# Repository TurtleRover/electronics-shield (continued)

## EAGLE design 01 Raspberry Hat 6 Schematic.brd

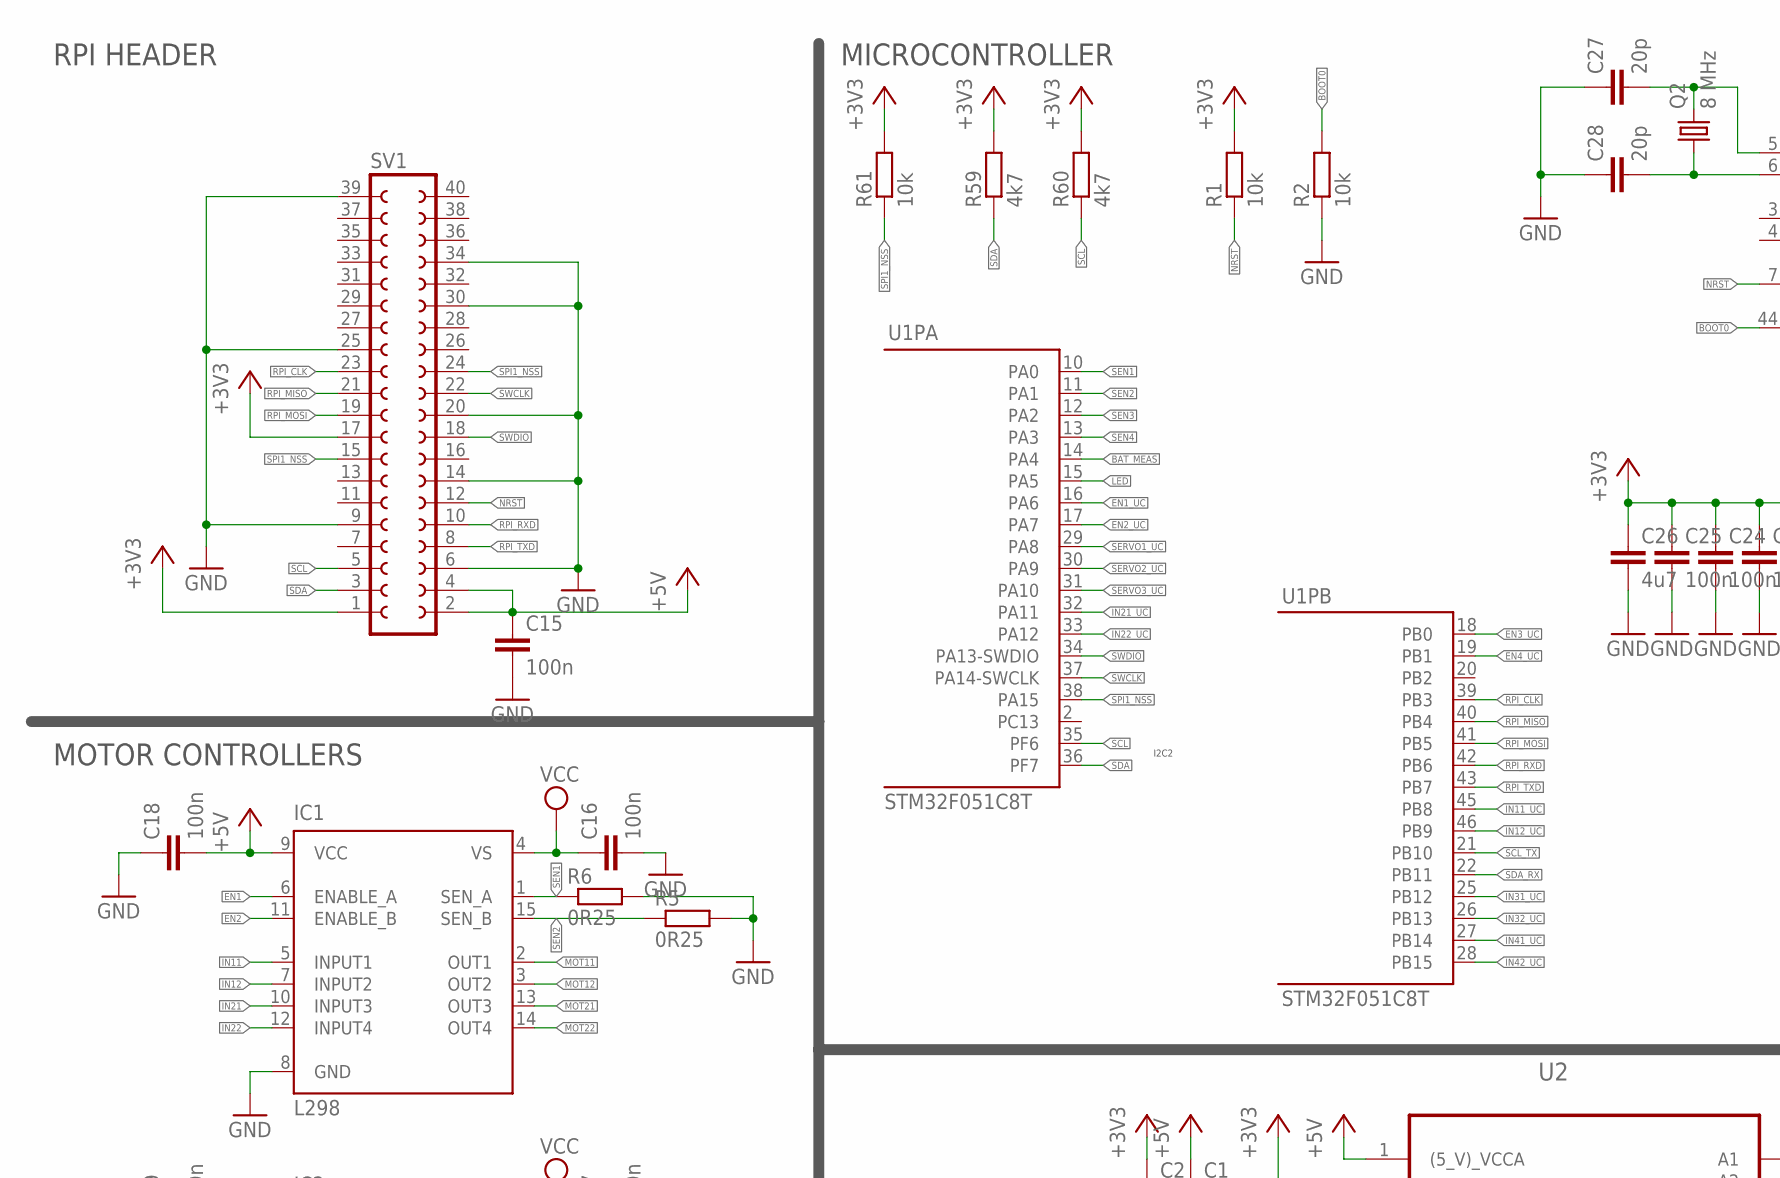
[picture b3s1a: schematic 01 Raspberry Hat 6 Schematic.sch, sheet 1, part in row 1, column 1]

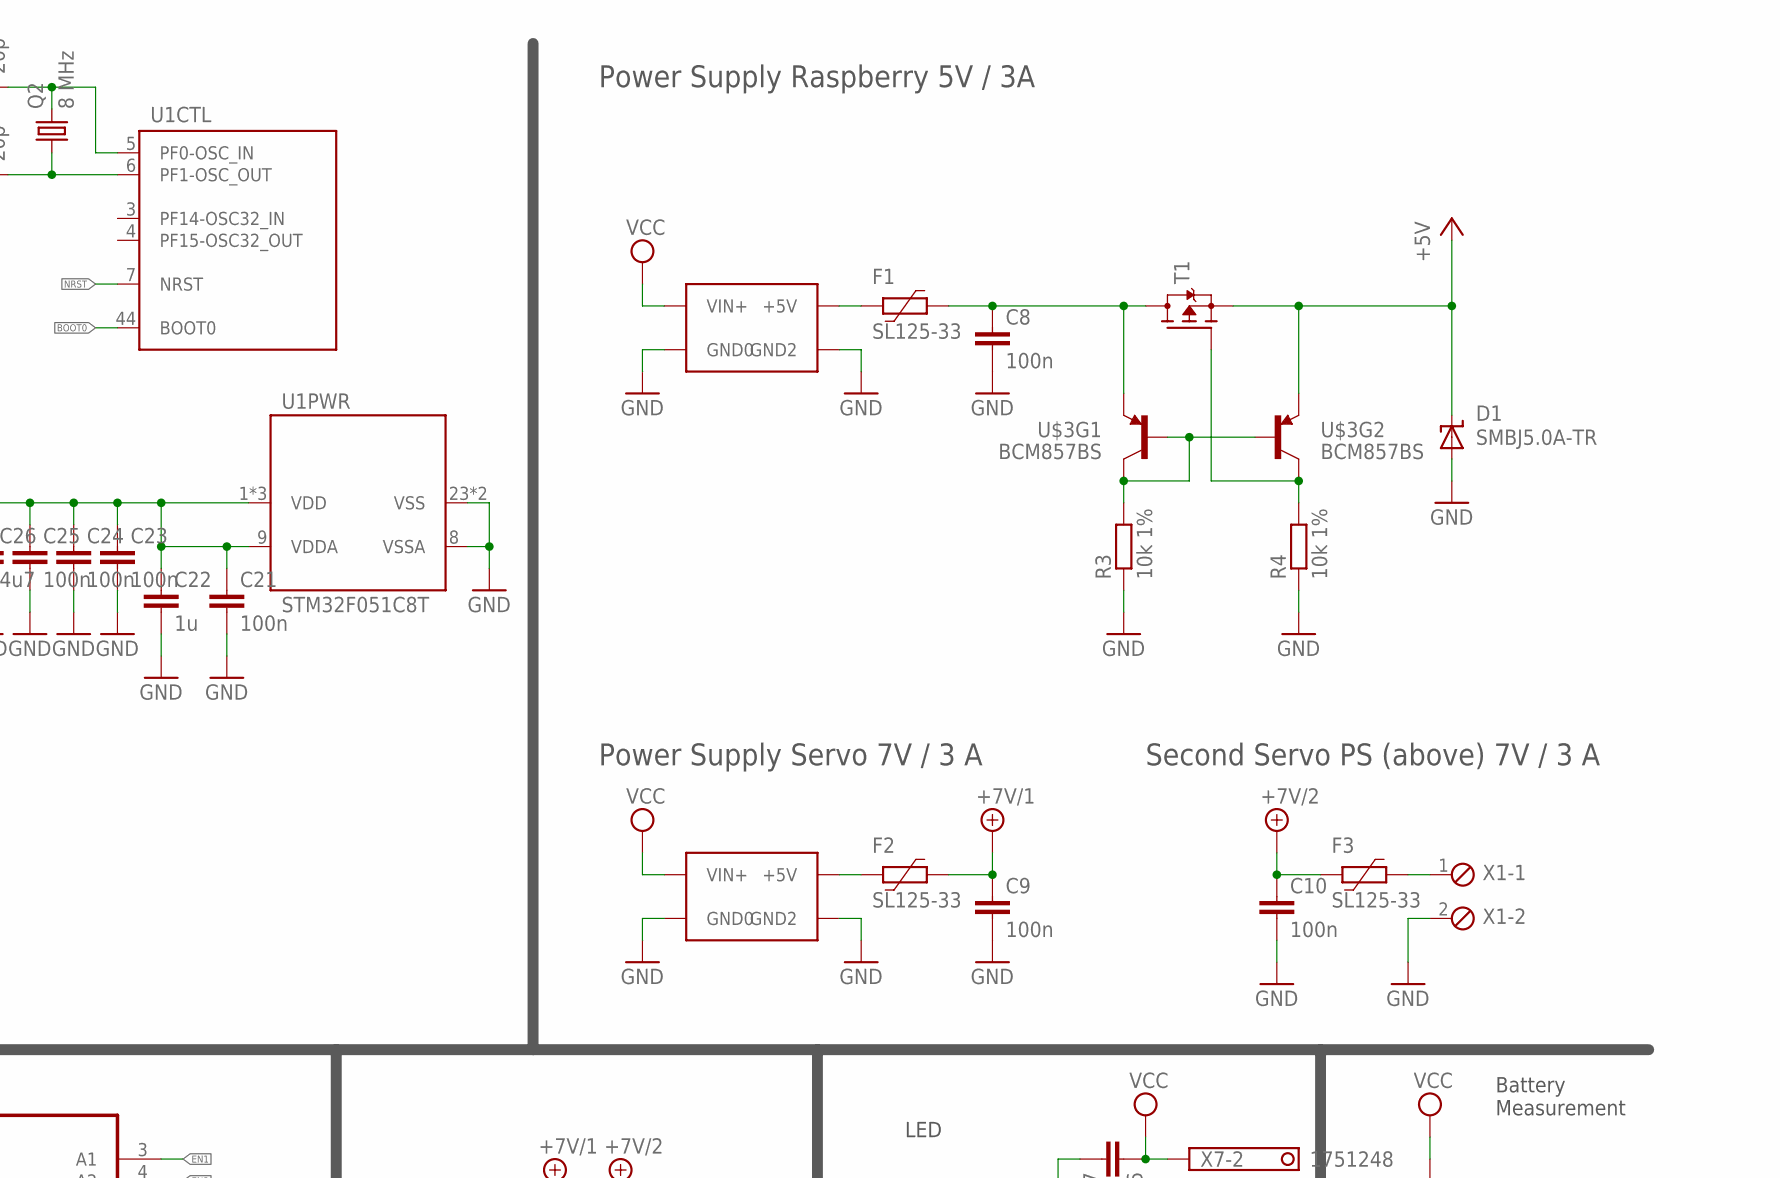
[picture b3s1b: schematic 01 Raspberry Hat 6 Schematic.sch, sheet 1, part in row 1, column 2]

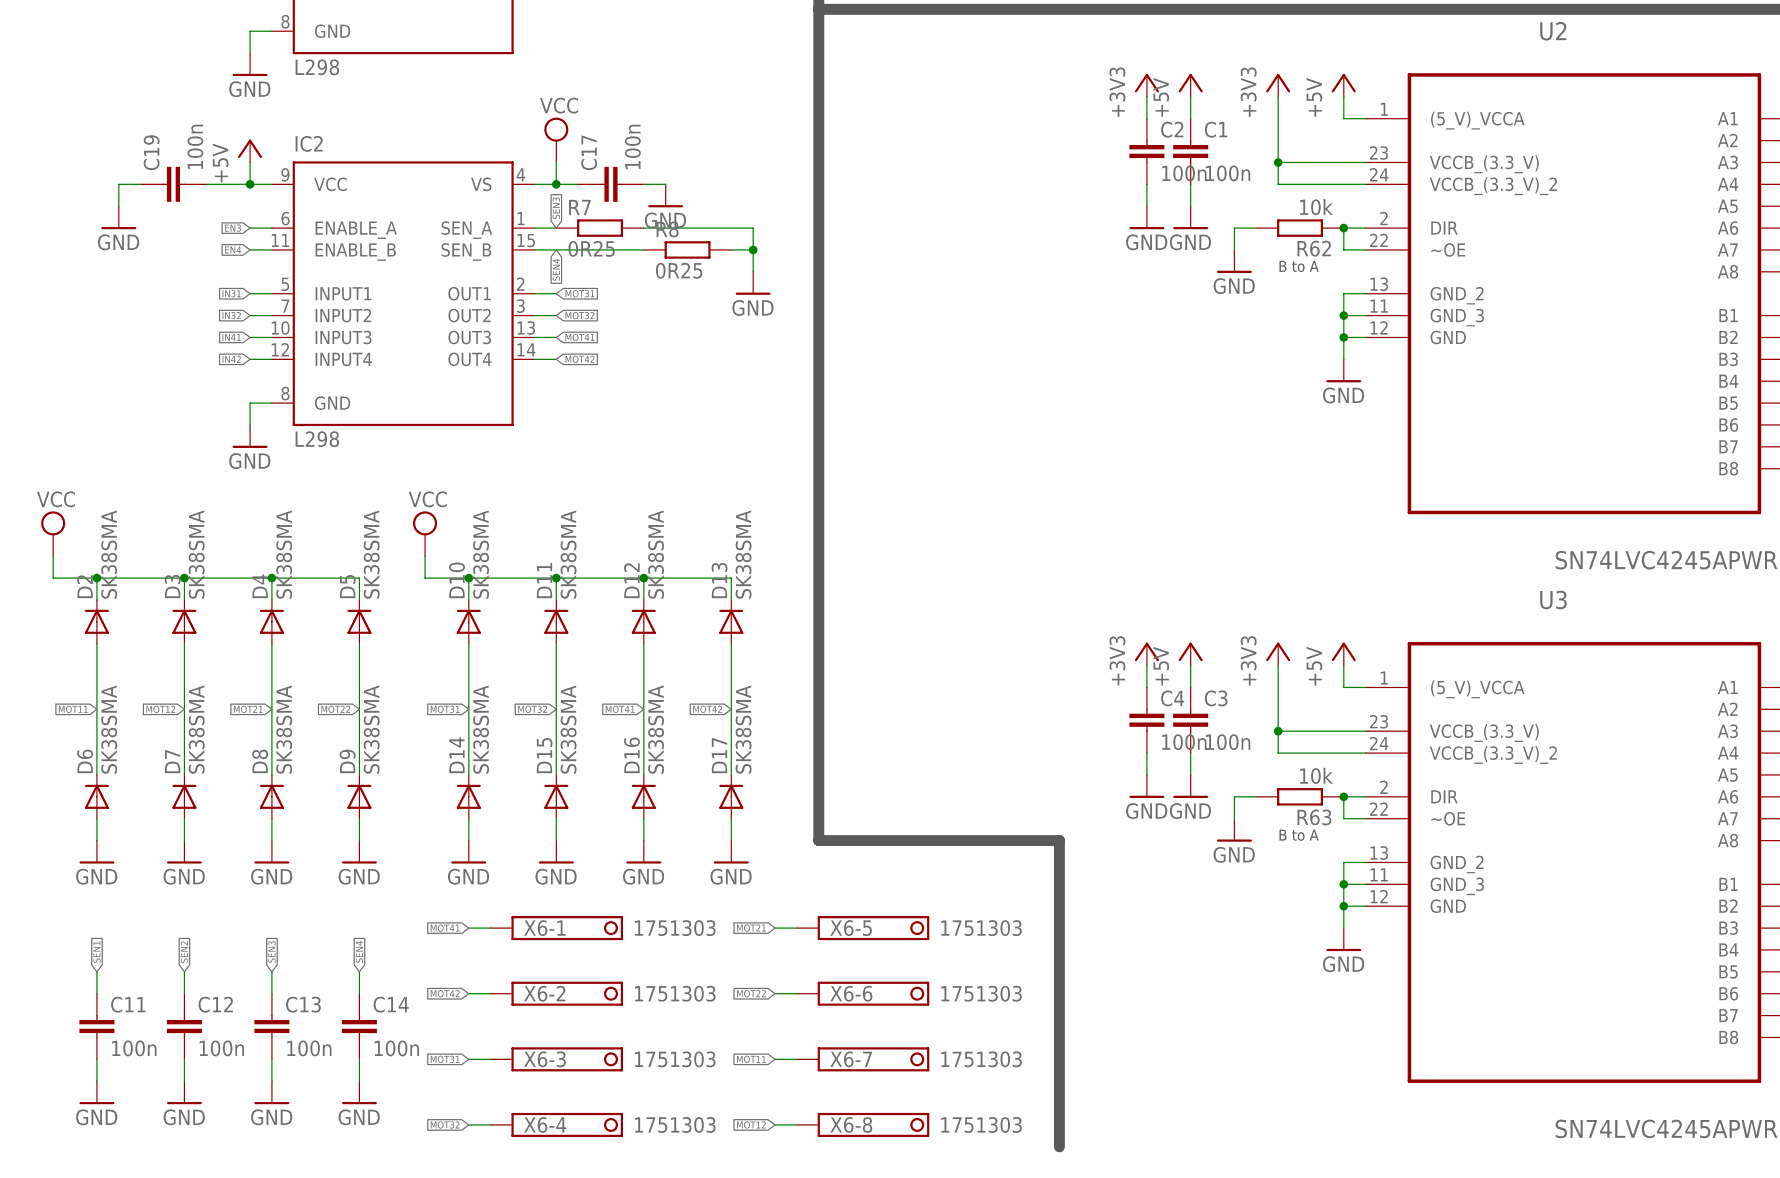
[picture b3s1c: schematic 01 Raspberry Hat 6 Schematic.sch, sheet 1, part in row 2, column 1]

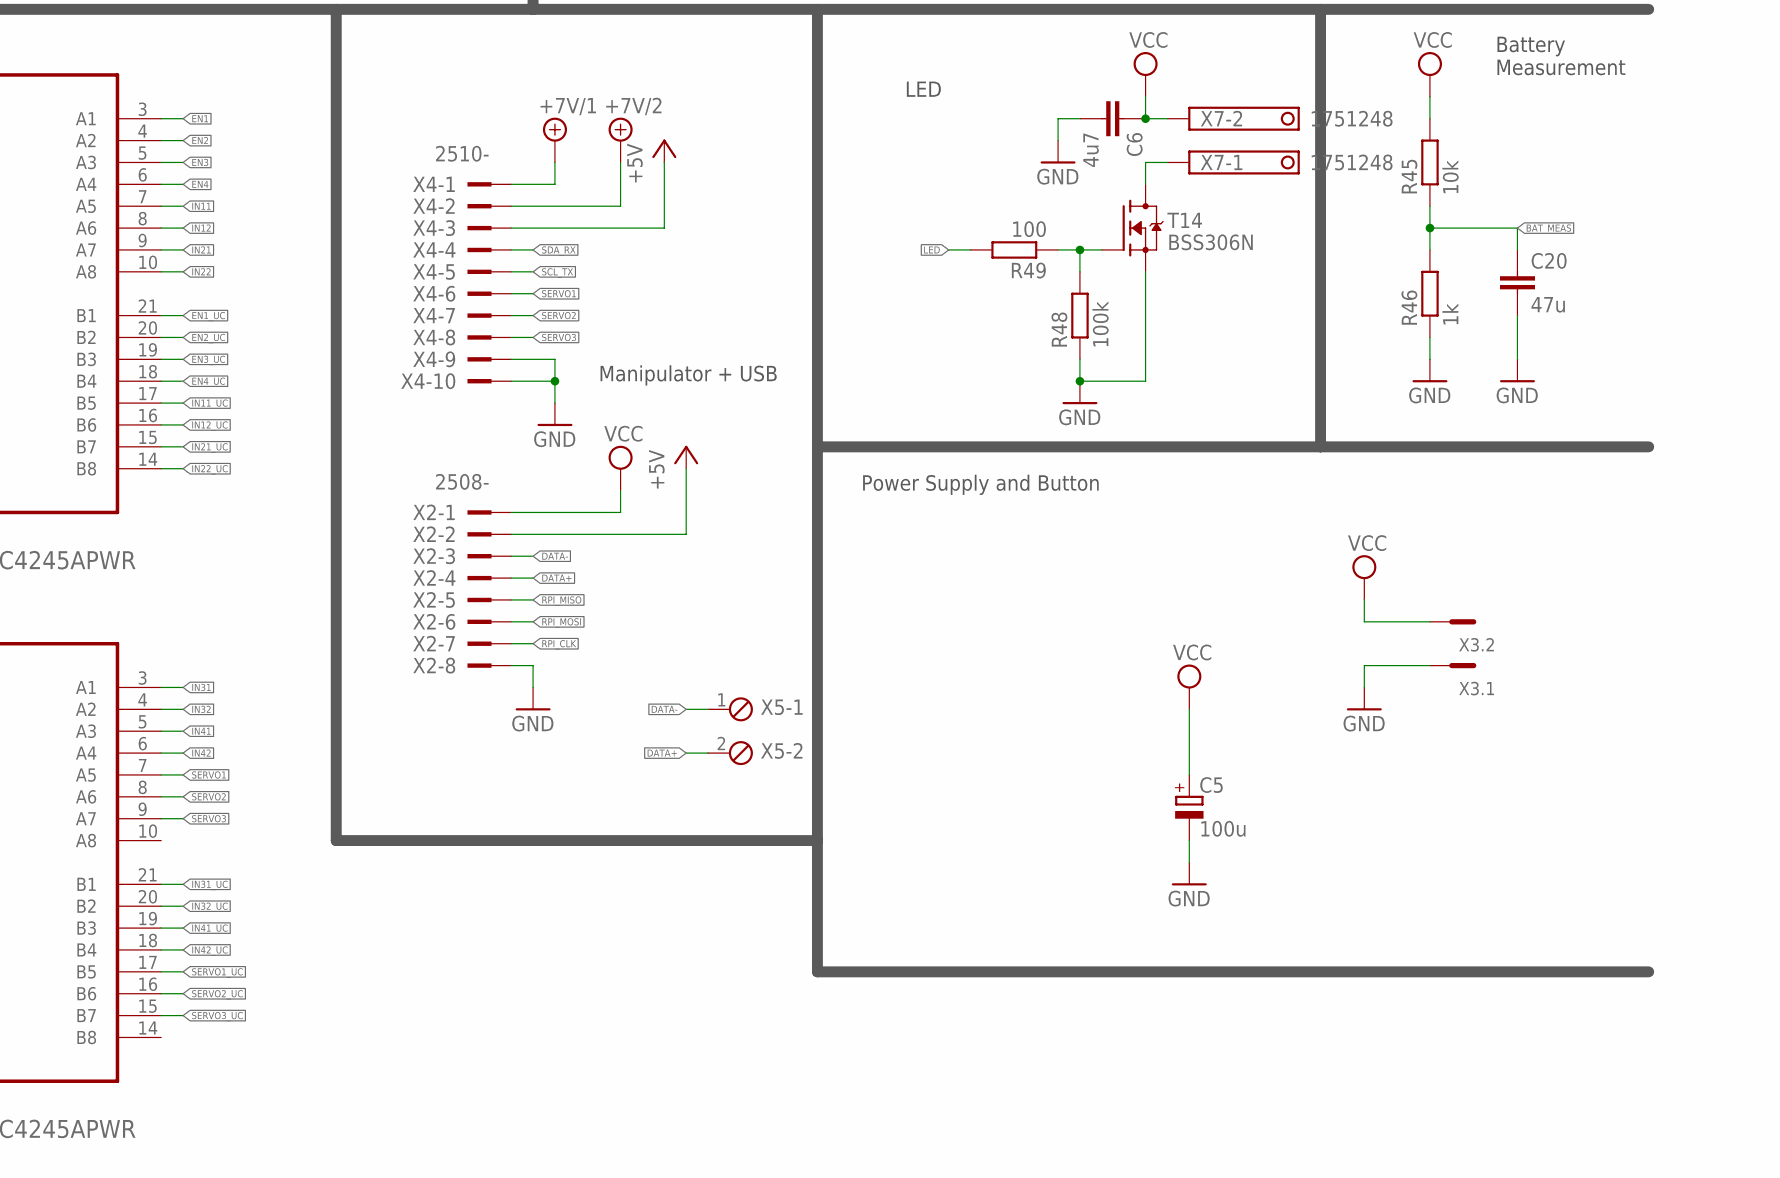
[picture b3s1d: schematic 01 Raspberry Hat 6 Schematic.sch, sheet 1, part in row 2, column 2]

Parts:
C1, C2, C3, C4, C8, C9, C10, C11, C12, C13, C14, C15, C16, C17, C18, C19, C21, C23, C24, C25: 100n; C0805
C5: 100u; 153CLV-0807
C6, C26: 4u7; C0805
C20: 47u; C0805
C22: 1u; C0805
C27, C28: 20p; C0805
D1: SMBJ5.0A-TR; SMBJ
D2, D3, D4, D5, D6, D7, D8, D9, D10, D11, D12, D13, D14, D15, D16, D17: SK38SMA; DO214AC
F1, F2, F3: SL125-33; 2920L
IC1, IC2: L298; MULTIWATT-15
Q2: 8 MHz; HC49UP
R1, R2, R45, R61, R62, R63: 10k; M0805
R3, R4: 10k 1%; M0805
R5, R6, R7, R8: 0R25; R2512
R46: 1k; M0805
R48: 100k; M0805
R49: 100; M0805
R59, R60: 4k7; M0805
SV1: FE20-2
T1: MOSFET-P-SOT23; SOT23
T14: BSS306N; SOT23
U1: STM32F051C8T; LQFP48
U2, U3: SN74LVC4245APWR; SOP65P640X120-24N
U$2, U$4: LM2596_CONVERTER
U$3: BCM857BS; SOT363
X1, X5: MPT2; 2POL254
X2: 2508-; PAK100/2500-10
X3: MC2
X4: 2510-; PAK100/2500-10
X6: 1751303
X7: 1751248

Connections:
+3V3: C2.1, C4.1, C21.1, C22.1, C23.1, C24.1, C25.1, C26.1, R1.2, R59.2, R60.2, R61.2, SV1.1, SV1.17, U1.1 (VDD), U1.9 (VDDA), U1.24 (VDD), U1.48 (VDD), U2.23 (VCCB_(3.3_V)), U2.24 (VCCB_(3.3_V)_2), U3.23 (VCCB_(3.3_V)), U3.24 (VCCB_(3.3_V)_2)
+5V: C1.1, C3.1, C15.1, C18.2, C19.2, D1.C, IC1.9 (VCC), IC2.9 (VCC), SV1.2, SV1.4, T1.2 (S), U2.1 ((5_V)_VCCA), U3.1 ((5_V)_VCCA), U$3.4 (E), X2.2, X4.3
+7V/1: C9.1, F2.1, X4.1
+7V/2: C10.1, F3.2, X4.2
BAT_MEAS: C20.1, R45.1, R46.2, U1.14 (PA4)
BOOT0: R2.2, U1.44 (BOOT0)
DATA+: X2.4, X5.2
DATA-: X2.3, X5.1
EN1: IC1.6 (ENABLE_A), U2.3 (A1)
EN1_UC: U1.16 (PA6), U2.21 (B1)
EN2: IC1.11 (ENABLE_B), U2.4 (A2)
EN2_UC: U1.17 (PA7), U2.20 (B2)
EN3: IC2.6 (ENABLE_A), U2.5 (A3)
EN3_UC: U1.18 (PB0), U2.19 (B3)
EN4: IC2.11 (ENABLE_B), U2.6 (A4)
EN4_UC: U1.19 (PB1), U2.18 (B4)
IN11: IC1.5 (INPUT1), U2.7 (A5)
IN11_UC: U1.45 (PB8), U2.17 (B5)
IN12: IC1.7 (INPUT2), U2.8 (A6)
IN12_UC: U1.46 (PB9), U2.16 (B6)
IN21: IC1.10 (INPUT3), U2.9 (A7)
IN21_UC: U1.32 (PA11), U2.15 (B7)
IN22: IC1.12 (INPUT4), U2.10 (A8)
IN22_UC: U1.33 (PA12), U2.14 (B8)
IN31: IC2.5 (INPUT1), U3.3 (A1)
IN31_UC: U1.25 (PB12), U3.21 (B1)
IN32: IC2.7 (INPUT2), U3.4 (A2)
IN32_UC: U1.26 (PB13), U3.20 (B2)
IN41: IC2.10 (INPUT3), U3.5 (A3)
IN41_UC: U1.27 (PB14), U3.19 (B3)
IN42: IC2.12 (INPUT4), U3.6 (A4)
IN42_UC: U1.28 (PB15), U3.18 (B4)
LED: R49.2, U1.15 (PA5)
MOT11: D2.A, D6.C, IC1.2 (OUT1), X6.7
MOT12: D3.A, D7.C, IC1.3 (OUT2), X6.8
MOT21: D4.A, D8.C, IC1.13 (OUT3), X6.5
MOT22: D5.A, D9.C, IC1.14 (OUT4), X6.6
MOT31: D10.A, D14.C, IC2.2 (OUT1), X6.3
MOT32: D11.A, D15.C, IC2.3 (OUT2), X6.4
MOT41: D12.A, D16.C, IC2.13 (OUT3), X6.1
MOT42: D13.A, D17.C, IC2.14 (OUT4), X6.2
unnamed: R62.1, U2.2 (DIR), U2.22 (~OE)
unnamed: R63.1, U3.2 (DIR), U3.22 (~OE)
unnamed: F1.2, U$2.+5V
unnamed: C8.1, F1.1, T1.3 (D), U$3.1 (E)
unnamed: F3.1, X1.1
unnamed: R4.2, T1.1 (G), U$3.3 (C)
unnamed: R3.2, U$3.2 (B), U$3.5 (B), U$3.6 (C)
unnamed: F2.2, U$4.+5V
unnamed: R48.2, R49.1, T14.1 (G)
unnamed: T14.3 (D), X7.1
unnamed: C28.2, Q2.1, U1.6 (PF1-OSC_OUT)
unnamed: C27.2, Q2.2, U1.5 (PF0-OSC_IN)
NRST: R1.1, SV1.12, U1.7 (NRST)
RPI_CLK: SV1.23, U1.39 (PB3), X2.7
RPI_MISO: SV1.21, U1.40 (PB4), X2.5
RPI_MOSI: SV1.19, U1.41 (PB5), X2.6
RPI_RXD: SV1.10, U1.42 (PB6)
RPI_TXD: SV1.8, U1.43 (PB7)
SCL: R60.1, SV1.5, U1.35 (PF6)
SCL_TX: U1.21 (PB10), X4.5
SDA: R59.1, SV1.3, U1.36 (PF7)
SDA_RX: U1.22 (PB11), X4.4
SEN1: C11.1, IC1.1 (SEN_A), R6.1, U1.10 (PA0)
SEN2: C12.1, IC1.15 (SEN_B), R5.1, U1.11 (PA1)
SEN3: C13.1, IC2.1 (SEN_A), R7.1, U1.12 (PA2)
SEN4: C14.1, IC2.15 (SEN_B), R8.1, U1.13 (PA3)
SERVO1: U3.7 (A5), X4.6
SERVO1_UC: U1.29 (PA8), U3.17 (B5)
SERVO2: U3.8 (A6), X4.7
SERVO2_UC: U1.30 (PA9), U3.16 (B6)
SERVO3: U3.9 (A7), X4.8
SERVO3_UC: U1.31 (PA10), U3.15 (B7)
SPI1_NSS: R61.1, SV1.15, SV1.24, U1.38 (PA15)
SWCLK: SV1.22, U1.37 (PA14-SWCLK)
SWDIO: SV1.18, U1.34 (PA13-SWDIO)

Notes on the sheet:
RPI HEADER
Power Supply Raspberry 5V / 3A
Power Supply Servo 7V / 3 A
Second Servo PS (above) 7V / 3 A
MOTOR CONTROLLERS
MICROCONTROLLER
Battery Measurement
Power Supply and Button
LED
I2C2
B to A
Manipulator + USB

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
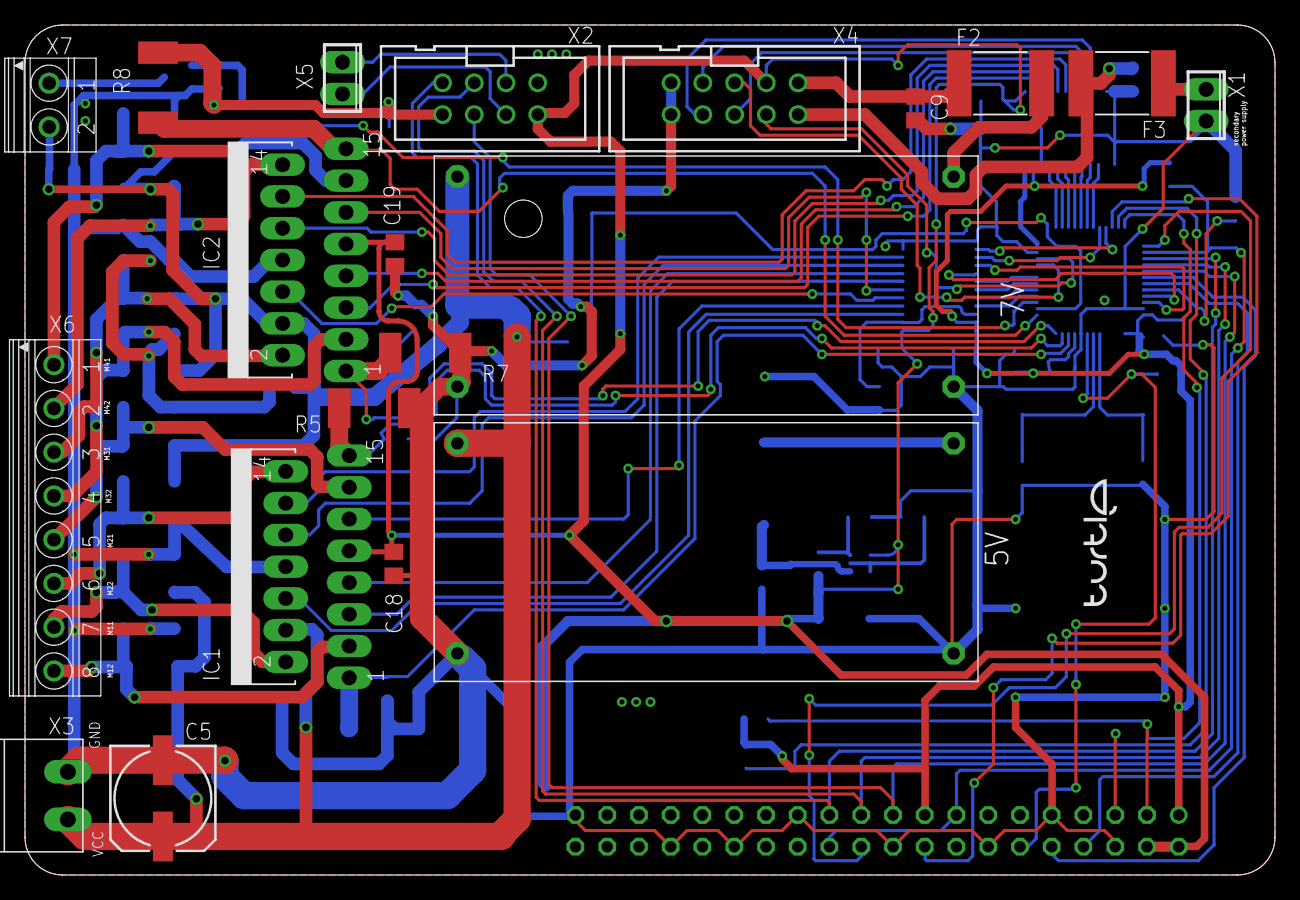
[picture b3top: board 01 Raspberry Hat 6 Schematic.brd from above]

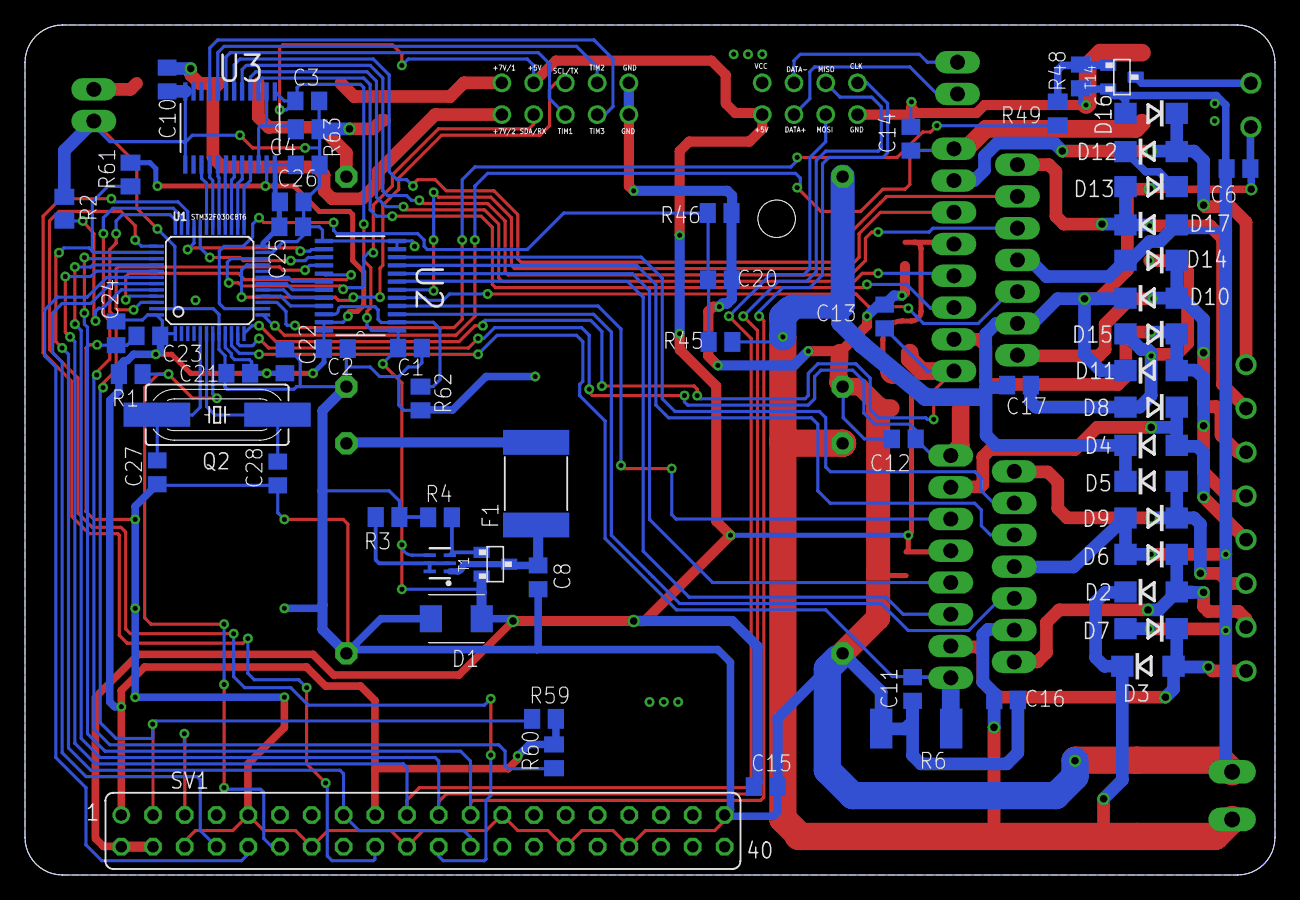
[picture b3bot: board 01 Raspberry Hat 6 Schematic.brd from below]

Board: 2 copper layers, 100.0 x 68.0 mm, 83 parts (63 on the bottom side), 78 nets.

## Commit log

2017-08-11 Create LICENSE
2018-07-19 Upload version 5.0.0
2018-07-19 Upload version 6.0.0
2018-07-19 Upload version 7.0.0
2018-07-20 Cleaning
2018-07-20 Start new version 8.x.x
2018-08-02 H-Bridge change from L298P to TLE9201S, better wiring
2018-08-10 Backlink to CADLAB.io has been added.
2018-08-11 Changed USB connector from two holes to micro-usb connector, change in voltage translation
2018-08-13 update copyright
2018-08-14 First conception of revision C, ~90% done, added 3D models for most of parts
2018-08-14 Recovering afret fuckup
2018-08-14 Adding project file
2018-08-14 Thermal vias and led for checking voltages added
2018-08-16 change few footprints, complete wiring
2018-08-18 changed base for 7.c
2018-08-28 Changed microprocessor, major and minor changes
2018-09-26 Added place to solder additional DC/DC converter, removed PTC from serwo power lines
2018-10-29 Removed DC-DC modules, gitignore added
2018-10-30 Basic schematic without pcb layout and values for parts
2018-10-30 Merge branch 'implement_dc_dc_converter' into development
    Added to schematic, basic place choosen
2018-10-30 Merge branch 'add_RTC' into development
    First, basic layout
2018-12-17 7C+ release
2018-12-18 Auto stash before rebase of "origin/master"
    Removed unnecessary files
2018-12-27 Added values for parts in dc-dc converter
2019-01-06 Minor changes, changed RTC, added 3V3 regulator, changed USB connector, added fuses, reverse polarity protection, changed footprint for Schottky diodes, added filtering to input voltage, change in la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
2019-01-31 Removed unnecessary stuff, cleaning
2019-02-17 Basic placement of rest of components
2019-02-17 Finish wiring, DRC done
2019-02-18 Font resize
2019-02-18 Change in description layout
